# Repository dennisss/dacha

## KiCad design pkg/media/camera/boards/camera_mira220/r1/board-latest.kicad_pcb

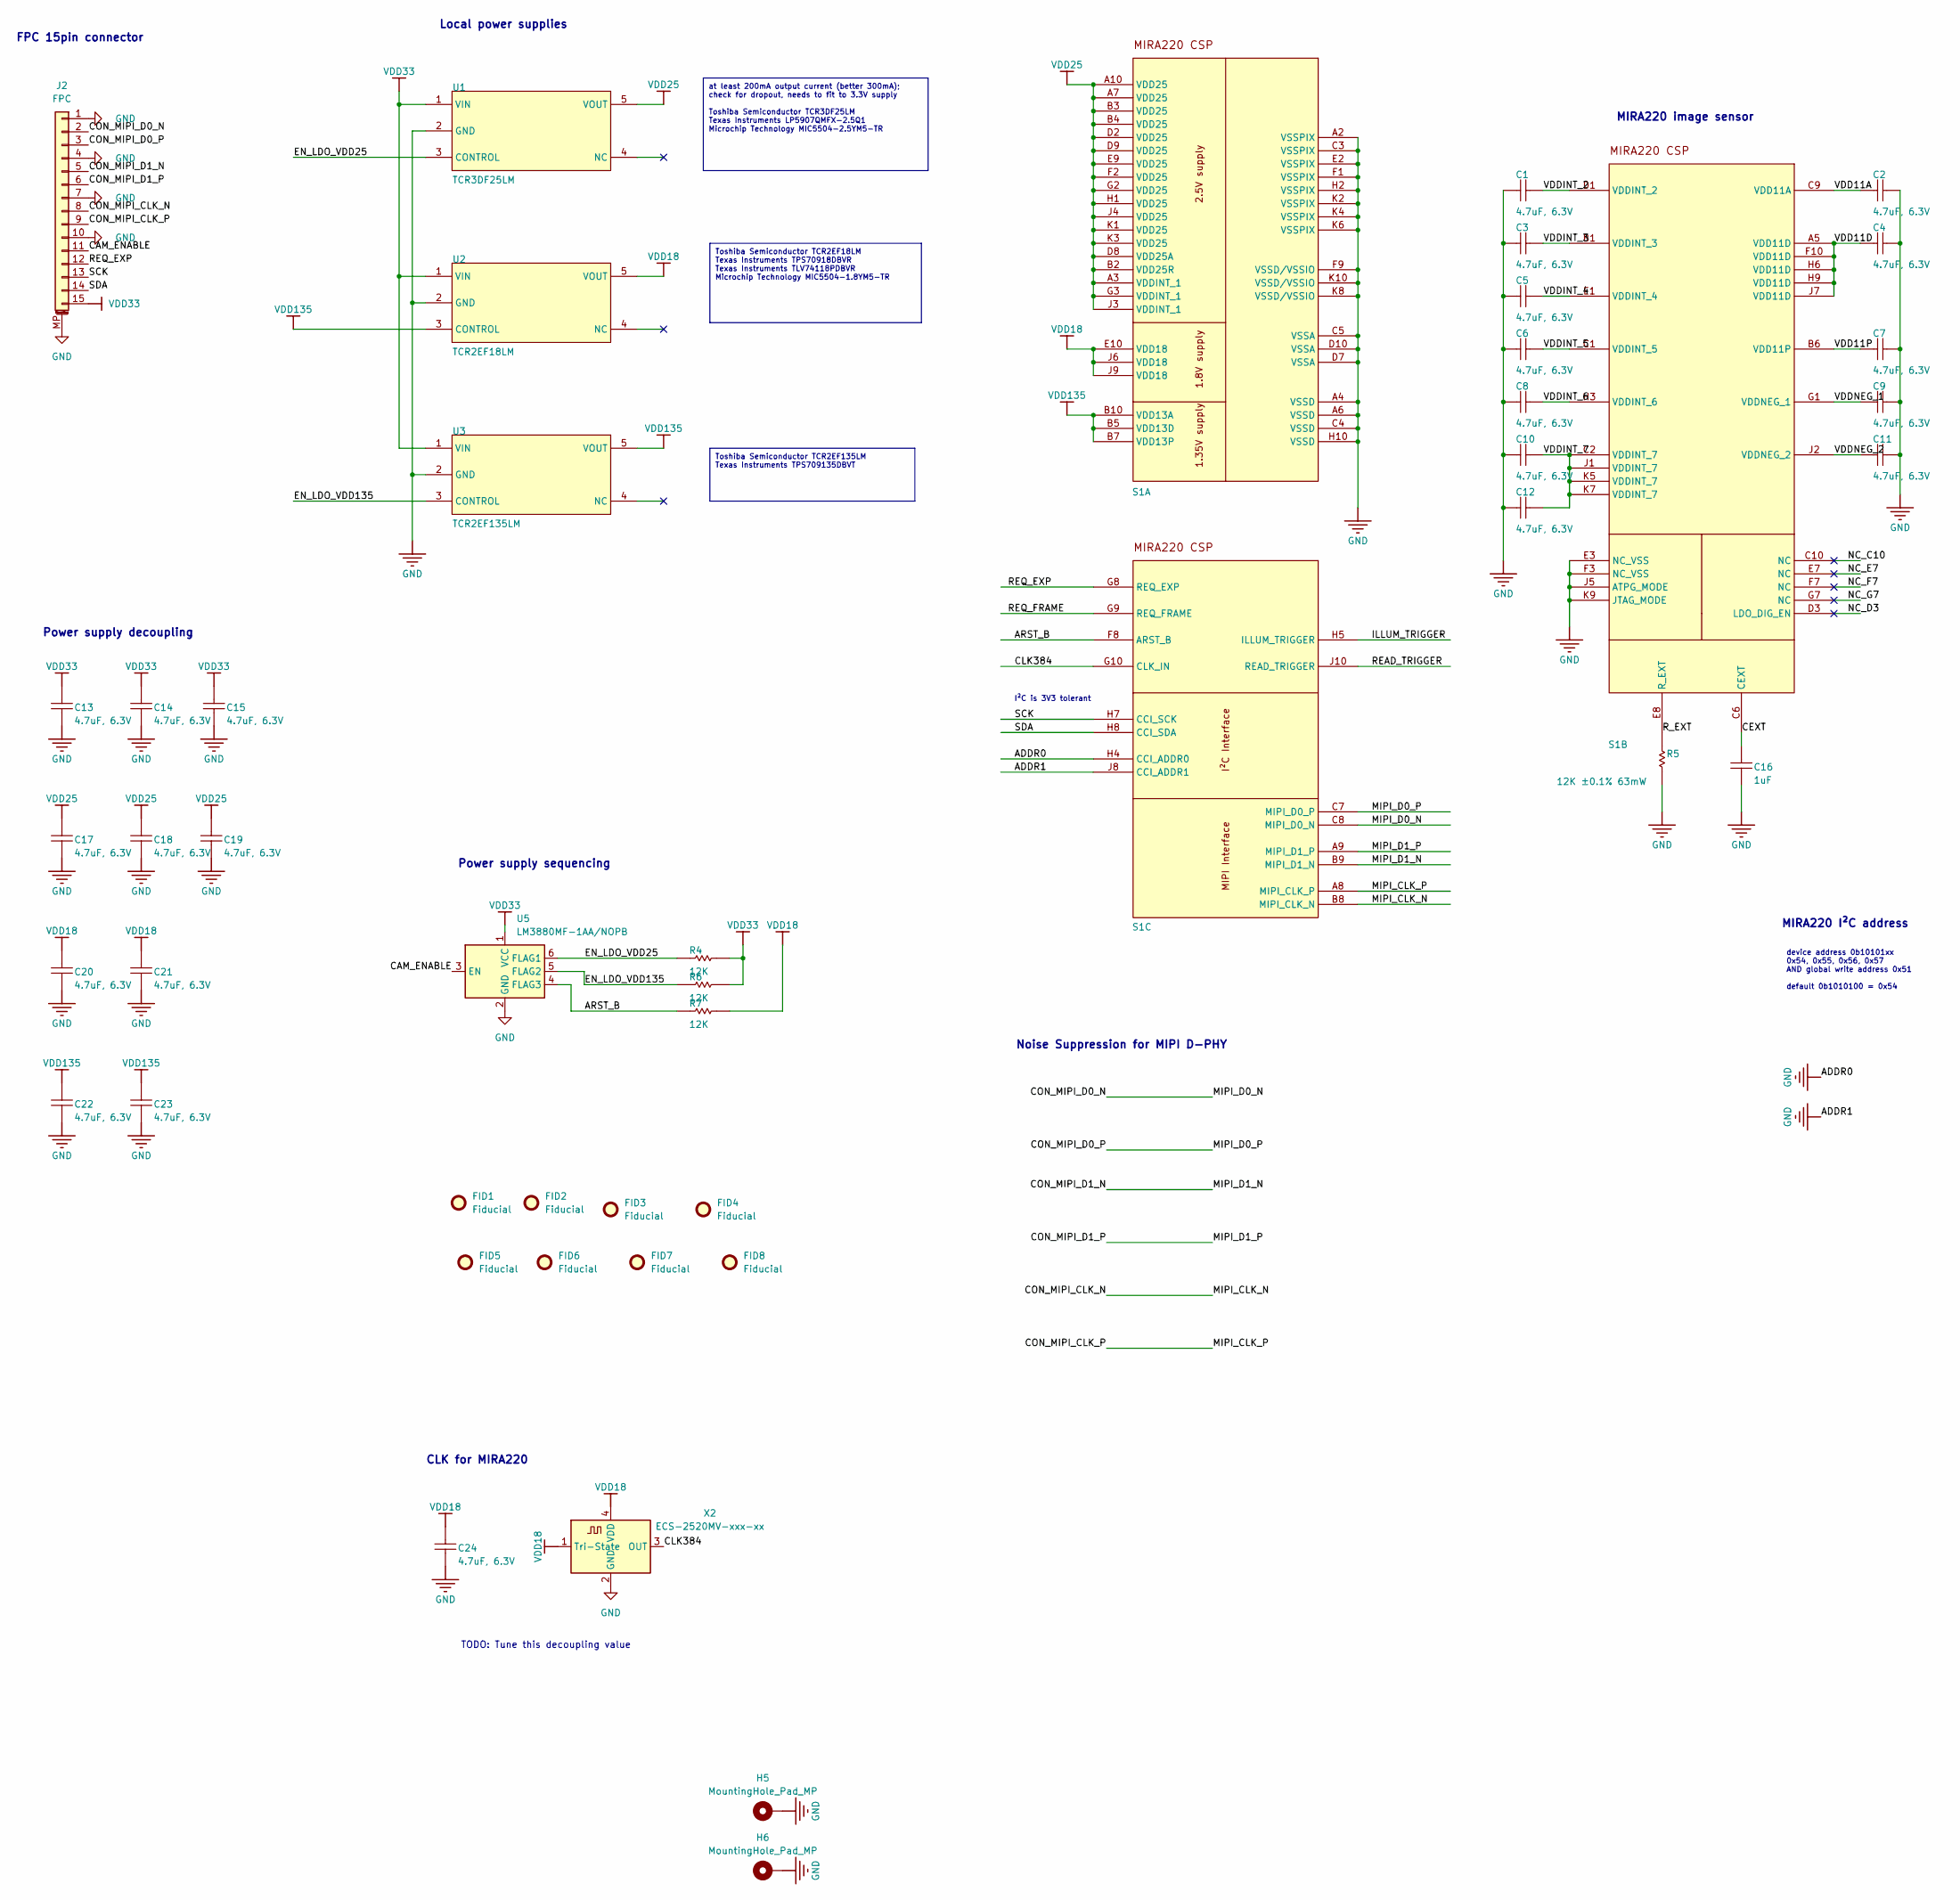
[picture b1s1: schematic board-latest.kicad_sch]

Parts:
C1, C2, C3, C4, C5, C6, C7, C8, C9, C10, C11, C13, C14, C15, C17, C18, C19, C20, C21, C22, C23, C24: 4.7uF, 6.3V; C_0402_1005Metric; RATED VOLTAGE 6.3; TOLERANCE ±10%; PART NUMBER GRM155R60J475ME47D
C12: 4.7uF, 6.3V; C_0402_1005Metric; RATED VOLTAGE 16 V; TOLERANCE ±10%; PART NUMBER GRM155R60J475ME47D
C16: 1uF; C_0402_1005Metric; PART NUMBER GRM155R70J105KA12J
FID1, FID2, FID3, FID4, FID5, FID6, FID7, FID8: Fiducial; Fiducial_1mm_Mask2mm
H5, H6: MountingHole_Pad_MP; MP_Lens
J2: FPC; TE_1-84952-5_1x15-1MP_P1.0mm_Horizontal
R4, R6, R7: 12K; R_0402_1005Metric; TOLERANCE ±0.1%; VOLTAGERATING 50V; PART NUMBER ERA2AEB123X
R5: 12K ±0.1% 63mW; R_0402_1005Metric; TOLERANCE ±0.1%; VOLTAGERATING 50V; PART NUMBER ERA2AEB123X
S1: MIRA CSP; MIRA220CSP; PART NUMBER Mira220-2QM1WA
U1: TCR3DF25LM; SC-74A-5_1.55x2.9mm_P0.95mm
U2: TCR2EF18LM; SC-74A-5_1.55x2.9mm_P0.95mm
U3: TCR2EF135LM; SC-74A-5_1.55x2.9mm_P0.95mm
U5: LM3880MF-1AA/NOPB; SOT-23-6
X2: ECS-2520MV-xxx-xx; Oscillator_SMD_ECS_2520MV-xxx-xx-4Pin_2.5x2.0mm

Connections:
/ARST_B: R7.2, S1.F8 (ARST_B), U5.4 (FLAG3)
/CAM_ENABLE: J2.11, U5.3 (EN)
/CEXT: C16.2, S1.C6 (CEXT)
/CLK384: S1.G10 (CLK_IN), X2.3 (OUT)
/CON_MIPI_CLK_N: J2.8, S1.B8 (MIPI_CLK_N)
/CON_MIPI_CLK_P: J2.9, S1.A8 (MIPI_CLK_P)
/CON_MIPI_D0_N: J2.2, S1.C8 (MIPI_D0_N)
/CON_MIPI_D0_P: J2.3, S1.C7 (MIPI_D0_P)
/CON_MIPI_D1_N: J2.5, S1.B9 (MIPI_D1_N)
/CON_MIPI_D1_P: J2.6, S1.A9 (MIPI_D1_P)
/EN_LDO_VDD25: R4.2, U1.3 (CONTROL), U5.6 (FLAG1)
/EN_LDO_VDD135: R6.2, U3.3 (CONTROL), U5.5 (FLAG2)
/ILLUM_TRIGGER: S1.H5 (ILLUM_TRIGGER)
/NC_C10: S1.C10 (NC)
/NC_D3: S1.D3 (LDO_DIG_EN)
/NC_E7: S1.E7 (NC)
/NC_F7: S1.F7 (NC)
/NC_G7: S1.G7 (NC)
/READ_TRIGGER: S1.J10 (READ_TRIGGER)
/REQ_EXP: J2.12, S1.G8 (REQ_EXP)
/REQ_FRAME: S1.G9 (REQ_FRAME)
/R_EXT: R5.2, S1.E8 (R_EXT)
/SCK: J2.13, S1.H7 (CCI_SCK)
/SDA: J2.14, S1.H8 (CCI_SDA)
/VDD11A: C2.1, S1.C9 (VDD11A)
/VDD11D: C4.1, S1.A5 (VDD11D), S1.F10 (VDD11D), S1.H6 (VDD11D), S1.H9 (VDD11D), S1.J7 (VDD11D)
/VDD11P: C7.1, S1.B6 (VDD11P)
/VDDINT_2: C1.2, S1.D1 (VDDINT_2)
/VDDINT_3: C3.2, S1.B1 (VDDINT_3)
/VDDINT_4: C5.2, S1.E1 (VDDINT_4)
/VDDINT_5: C6.2, S1.C1 (VDDINT_5)
/VDDINT_6: C8.2, S1.H3 (VDDINT_6)
/VDDINT_7: C10.2, C12.2, S1.C2 (VDDINT_7), S1.J1 (VDDINT_7), S1.K5 (VDDINT_7), S1.K7 (VDDINT_7)
/VDDNEG_1: C9.1, S1.G1 (VDDNEG_1)
/VDDNEG_2: C11.1, S1.J2 (VDDNEG_2)
GND: C1.1, C2.2, C3.1, C4.2, C5.1, C6.1, C7.2, C8.1, C9.2, C10.1, C11.2, C12.1, C13.1, C14.1, C15.1, C16.1, C17.1, C18.1, C19.1, C20.1, C21.1, C22.1, C23.1, C24.1, H5.MP, H6.MP, J2.1, J2.4, J2.7, J2.10, J2.MP (MountPin), R5.1, S1.A2 (VSSPIX), S1.A4 (VSSD), S1.A6 (VSSD), S1.C3 (VSSPIX), S1.C4 (VSSD), S1.C5 (VSSA), S1.D7 (VSSA), S1.D10 (VSSA), S1.E2 (VSSPIX), S1.E3 (NC_VSS), S1.F1 (VSSPIX), S1.F3 (NC_VSS), S1.F9 (VSSD/VSSIO), S1.H2 (VSSPIX), S1.H4 (CCI_ADDR0), S1.H10 (VSSD), S1.J5 (ATPG_MODE), S1.J8 (CCI_ADDR1), S1.K2 (VSSPIX), S1.K4 (VSSPIX), S1.K6 (VSSPIX), S1.K8 (VSSD/VSSIO), S1.K9 (JTAG_MODE), S1.K10 (VSSD/VSSIO), U1.2 (GND), U2.2 (GND), U3.2 (GND), U5.2 (GND), X2.2 (GND)
VDD18: C20.2, C21.2, C24.2, R7.1, S1.E10 (VDD18), S1.J6 (VDD18), S1.J9 (VDD18), U2.5 (VOUT), X2.1 (Tri-State), X2.4 (VDD)
VDD25: C17.2, C18.2, C19.2, S1.A3 (VDDINT_1), S1.A7 (VDD25), S1.A10 (VDD25), S1.B2 (VDD25R), S1.B3 (VDD25), S1.B4 (VDD25), S1.D2 (VDD25), S1.D8 (VDD25A), S1.D9 (VDD25), S1.E9 (VDD25), S1.F2 (VDD25), S1.G2 (VDD25), S1.G3 (VDDINT_1), S1.H1 (VDD25), S1.J3 (VDDINT_1), S1.J4 (VDD25), S1.K1 (VDD25), S1.K3 (VDD25), U1.5 (VOUT)
VDD33: C13.2, C14.2, C15.2, J2.15, R4.1, R6.1, U1.1 (VIN), U2.1 (VIN), U3.1 (VIN), U5.1 (VCC)
VDD135: C22.2, C23.2, S1.B5 (VDD13D), S1.B7 (VDD13P), S1.B10 (VDD13A), U2.3 (CONTROL), U3.5 (VOUT)

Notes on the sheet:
MIRA220 image sensor
I²C is 3V3 tolerant
Noise Suppression for MIPI D-PHY
Power supply decoupling
MIRA220 I²C address
Power supply sequencing
TODO: Tune this decoupling value
CLK for MIRA220
Local power supplies
FPC 15pin connector
at least 200mA output current (better 300mA); check for dropout, needs to fit to 3.3V supply Toshiba Semiconductor TCR3DF25LM Texas Instruments LP5907QMFX-2.5Q1 Microchip Technology MIC5504-2.5YM5-TR
device address 0b10101xx 0x54, 0x55, 0x56, 0x57 AND global write address 0x51 default 0b1010100 = 0x54
Toshiba Semiconductor TCR2EF18LM Texas Instruments TPS70918DBVR Texas Instruments TLV74118PDBVR Microchip Technology MIC5504-1.8YM5-TR
Toshiba Semiconductor TCR2EF135LM Texas Instruments TPS709135DBVT

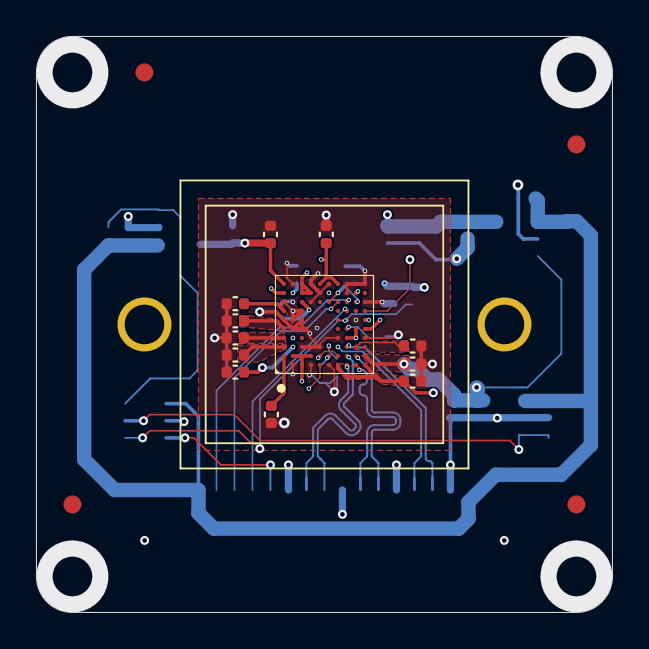
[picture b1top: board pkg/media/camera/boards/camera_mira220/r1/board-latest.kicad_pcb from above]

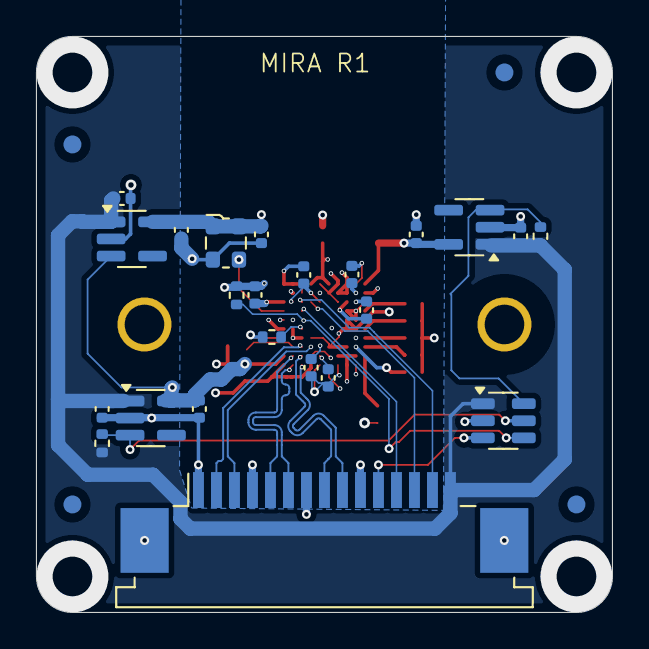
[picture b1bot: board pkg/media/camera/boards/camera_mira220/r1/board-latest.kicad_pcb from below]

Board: 6 copper layers, 32.0 x 32.0 mm, 45 parts (27 on the bottom side), 32 nets.

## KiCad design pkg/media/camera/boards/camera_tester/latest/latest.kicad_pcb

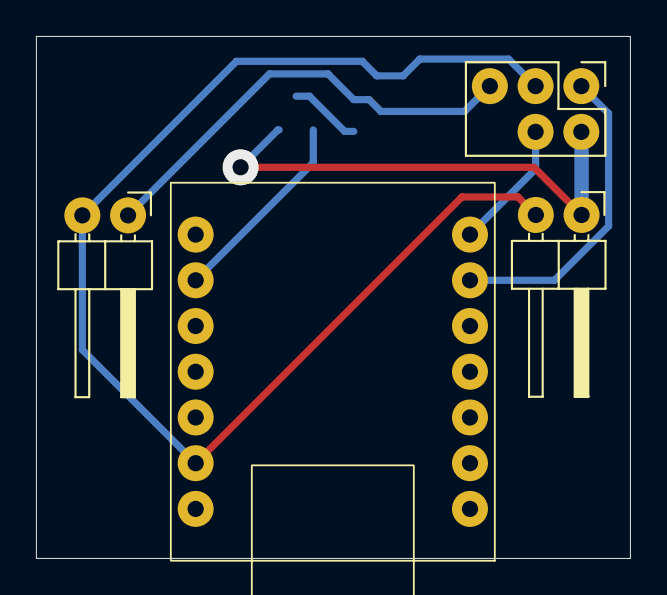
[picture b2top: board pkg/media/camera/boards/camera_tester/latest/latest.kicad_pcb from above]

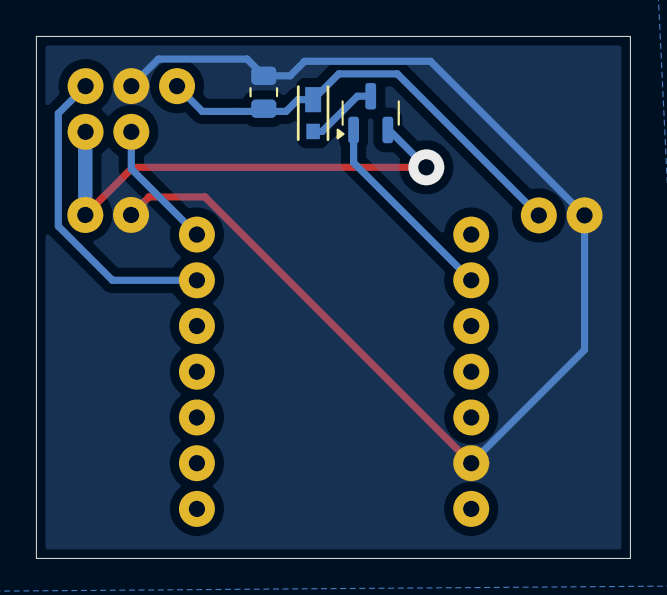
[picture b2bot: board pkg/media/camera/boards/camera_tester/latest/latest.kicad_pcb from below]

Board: 2 copper layers, 33.0 x 29.0 mm, 7 parts (3 on the bottom side), 7 nets.

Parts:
CR1: MSS1P3L-M3/89A; DIODE_MSP3V3
J1: FPC; PinHeader_2x03_P2.54mm_Vertical
J2: POWER; PinHeader_1x02_P2.54mm_Horizontal
J3: UDPI; PinHeader_1x02_P2.54mm_Horizontal
Q2: AO3401A; SOT-23
R1: 100K; R_0805_2012Metric
U1: XIAO_NRF52840

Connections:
+3V3: J1.2, J2.1, Q2.2 (S)
ENABLE: CR1.1, J1.5, J3.1, R1.1
ENABLE_DRIVE_HIGH: Q2.1 (G), U1.9 (P1.13)
GND: J1.3, J2.2, J3.2, R1.2, U1.13 (GND)
unnamed: CR1.2, Q2.3 (D)
SCL: J1.4, U1.7 (P1.11)
SDA: J1.1, U1.6 (P0.05(A5))

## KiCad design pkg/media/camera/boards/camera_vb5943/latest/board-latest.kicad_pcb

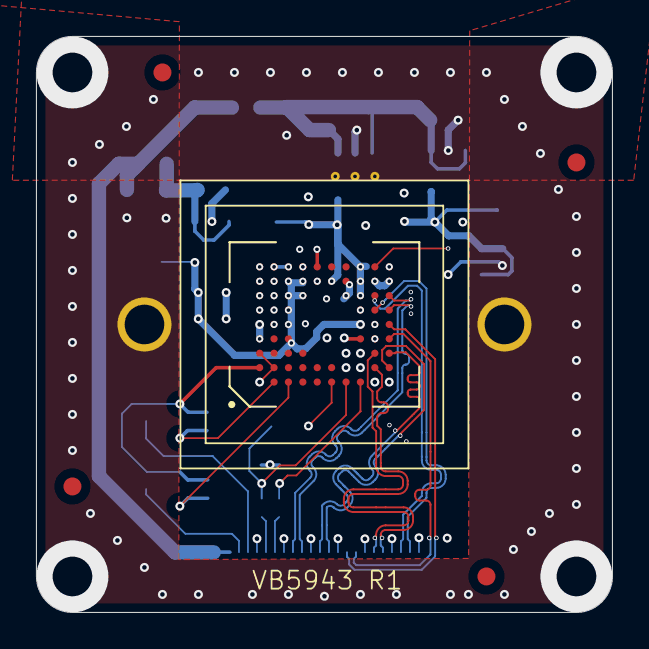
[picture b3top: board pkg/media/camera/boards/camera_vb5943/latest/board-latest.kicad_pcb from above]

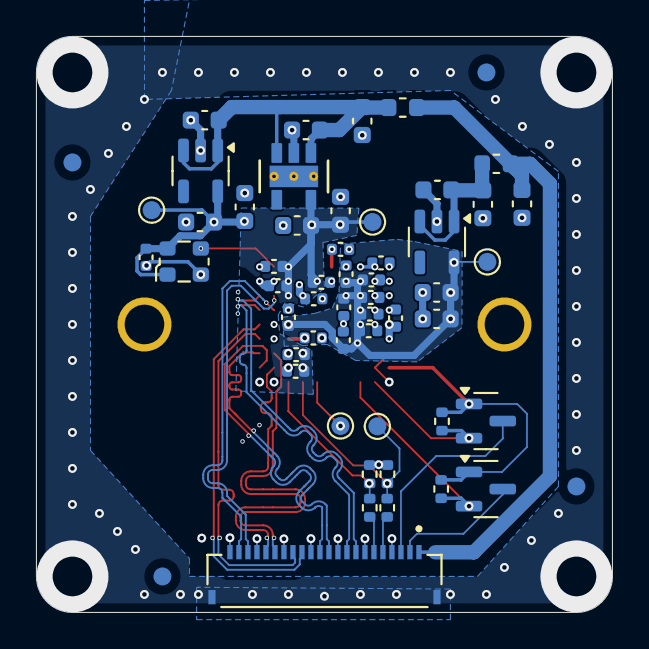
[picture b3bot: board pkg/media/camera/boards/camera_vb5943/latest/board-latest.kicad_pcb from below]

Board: 6 copper layers, 32.0 x 32.0 mm, 62 parts (55 on the bottom side), 31 nets.

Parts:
C1, C3, C4, C5, C6, C7, C8, C9, C20, C21, C29: 0.1uF; C_0402_1005Metric
C30, C31, C32, C33, C34, C35: 1uF; C_0603_1608Metric
C37, C38, C39, C40, C41, C50: 10uF; C_0603_1608Metric
C42: 4.7uF; C_0402_1005Metric
C43, C46, C47, C48: 470nF; C_0402_1005Metric
C44, C49: 1uF; C_0402_1005Metric
C45: 10uF; C_0402_1005Metric
FID1, FID2, FID3, FID4, FID5, FID6, FID7, FID8: Fiducial; Fiducial_1mm_Mask2mm
H5, H6: MountingHole_Pad_MP; MP_Lens
J1: FH34SRJ-22S-0.5SH_50_; HRS_FH34SRJ-22S-0.5SH_50_
L1, L2: 600 ohm; L_0603_1608Metric
Q1, Q2: BSS138; SOT-23
R2, R3, R4, R6, R14, R15: 1.5K; R_0402_1005Metric
TP1: FLASH; TestPoint_Pad_D1.0mm
TP2: TRIGGER; TestPoint_Pad_D1.0mm
TP3: 2V8; TestPoint_Pad_D1.0mm
TP4: 1V8; TestPoint_Pad_D1.0mm
TP5: 1V2; TestPoint_Pad_D1.0mm
U3: NCP163ASN280T1G; SOT-23-5
U4: TLV74318PDBVR; SOT-23-5
U5: TLV75512PDYDR; DYD0005A-MFG
U6: VB5943; VB5943_BGA
X1: ECS-2520MV-240-DN-TR; Oscillator_SMD_ECS_2520MV-xxx-xx-4Pin_2.5x2.0mm

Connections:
+1V2: C20.1, C21.1, C34.1, C38.1, C46.2, C47.2, C48.2, TP5.1, U5.5 (OUT), U6.F8 (VCORE), U6.G2 (VCORE), U6.G3 (VCORE), U6.H7 (VCORE), U6.H8 (VCORE), U6.H9 (VCORE)
+1V8: C29.1, C33.1, C49.1, C50.1, Q1.1 (G), Q2.1 (G), R4.2, R6.2, TP4.1, U4.5 (OUT), U6.A2 (CLK_RANGE0), U6.G7 (VDDIO), U6.G8 (VDDIO), X1.1 (Tri-State), X1.4 (VDD)
+2V8: C1.1, C3.1, C4.1, C5.1, C6.1, C7.1, C8.1, C9.1, C31.1, C37.1, TP3.1, U3.5 (OUT), U6.C4 (VANA), U6.C5 (VANA), U6.C6 (VANA), U6.C7 (VANA), U6.C8 (VANA), U6.D7 (VANA), U6.D8 (VANA), U6.H5 (VANA)
+3V3: C41.1, J1.1, L1.1, L2.1
ANALOG_3V3: C30.1, C39.1, L1.2, U3.1 (IN), U3.3 (EN)
DIGITAL_3V3: C32.1, C35.1, C40.1, L2.2, U4.1 (IN), U4.3 (EN), U5.1 (IN), U5.3 (EN)
ENABLE_1V8: R14.1, R15.2, U6.H1 (~RESET)
ENABLE_3V3: J1.6, R14.2
EXTCLK: U6.J9 (EXTCLK), X1.3 (OUT)
GND: C1.2, C3.2, C4.2, C5.2, C6.2, C7.2, C8.2, C9.2, C20.2, C21.2, C29.2, C30.2, C31.2, C32.2, C33.2, C34.2, C35.2, C37.2, C38.2, C39.2, C40.2, C41.2, C42.1, C43.1, C44.2, C45.2, C46.1, C47.1, C48.1, C49.2, C50.2, H5.MP, H6.MP, J1.4, J1.7, J1.10, J1.13, J1.16, J1.19, J1.22, J1.S1 (SHIELD), J1.S2 (SHIELD), R3.1, R15.1, U3.2 (GND), U4.2 (GND), U5.2 (GND), U6.A1 (AGND), U6.A3 (CLK_RANGE1), U6.A6 (AGND), U6.A7 (AGND), U6.A8 (AGND), U6.A9 (AGND), U6.B2 (PORTEST), U6.B5 (AGND), U6.B6 (AGND), U6.B7 (AGND), U6.B8 (AGND), U6.D9 (AGND), U6.E8 (DGND), U6.H2 (DGND), U6.H3 (DGND), U6.H6 (AGND), U6.J1 (DGND), U6.J4 (DGND), U6.J5 (DGND), U6.J8 (DGND), U6.K1 (DGND), U6.K8 (DGND), U6.K9 (DGND), X1.2 (GND)
MIPI_CLK_N: J1.15, U6.K4 (CLKN)
MIPI_CLK_P: J1.14, U6.K5 (CLKP)
MIPI_D0_N: J1.21, U6.J6 (DATA1N)
MIPI_D0_P: J1.20, U6.J7 (DATA1P)
MIPI_D1_N: J1.18, U6.J2 (DATA2N)
MIPI_D1_P: J1.17, U6.J3 (DATA2P)
MIPI_D2_N: J1.12, U6.K2 (DATA3N)
MIPI_D2_P: J1.11, U6.K3 (DATA3P)
MIPI_D3_N: J1.9, U6.K6 (DATA4N)
MIPI_D3_P: J1.8, U6.K7 (DATA4P)
unnamed: C45.1, U6.A4 (CP_NEG_OUT), U6.A5 (CP_NEG_IN)
unnamed: C44.1, U6.B9 (CP_POS_OUT), U6.C9 (CP_POS_IN)
unnamed: TP1.1, U6.F1 (GPIO1)
unnamed: C43.2, U6.H4 (LDO2V4)
unnamed: C42.2, U6.E9 (VRT)
SCL_1V8: Q1.2 (S), R4.1, U6.B1 (SCL)
SCL_3V3: J1.3, Q1.3 (D)
SDA_1V8: Q2.2 (S), R6.1, U6.C1 (SDA)
SDA_3V3: J1.2, Q2.3 (D)
TRIGGER_1V8: R2.1, R3.2, TP2.1, U6.G1 (GPIO0)
TRIGGER_3V3: J1.5, R2.2

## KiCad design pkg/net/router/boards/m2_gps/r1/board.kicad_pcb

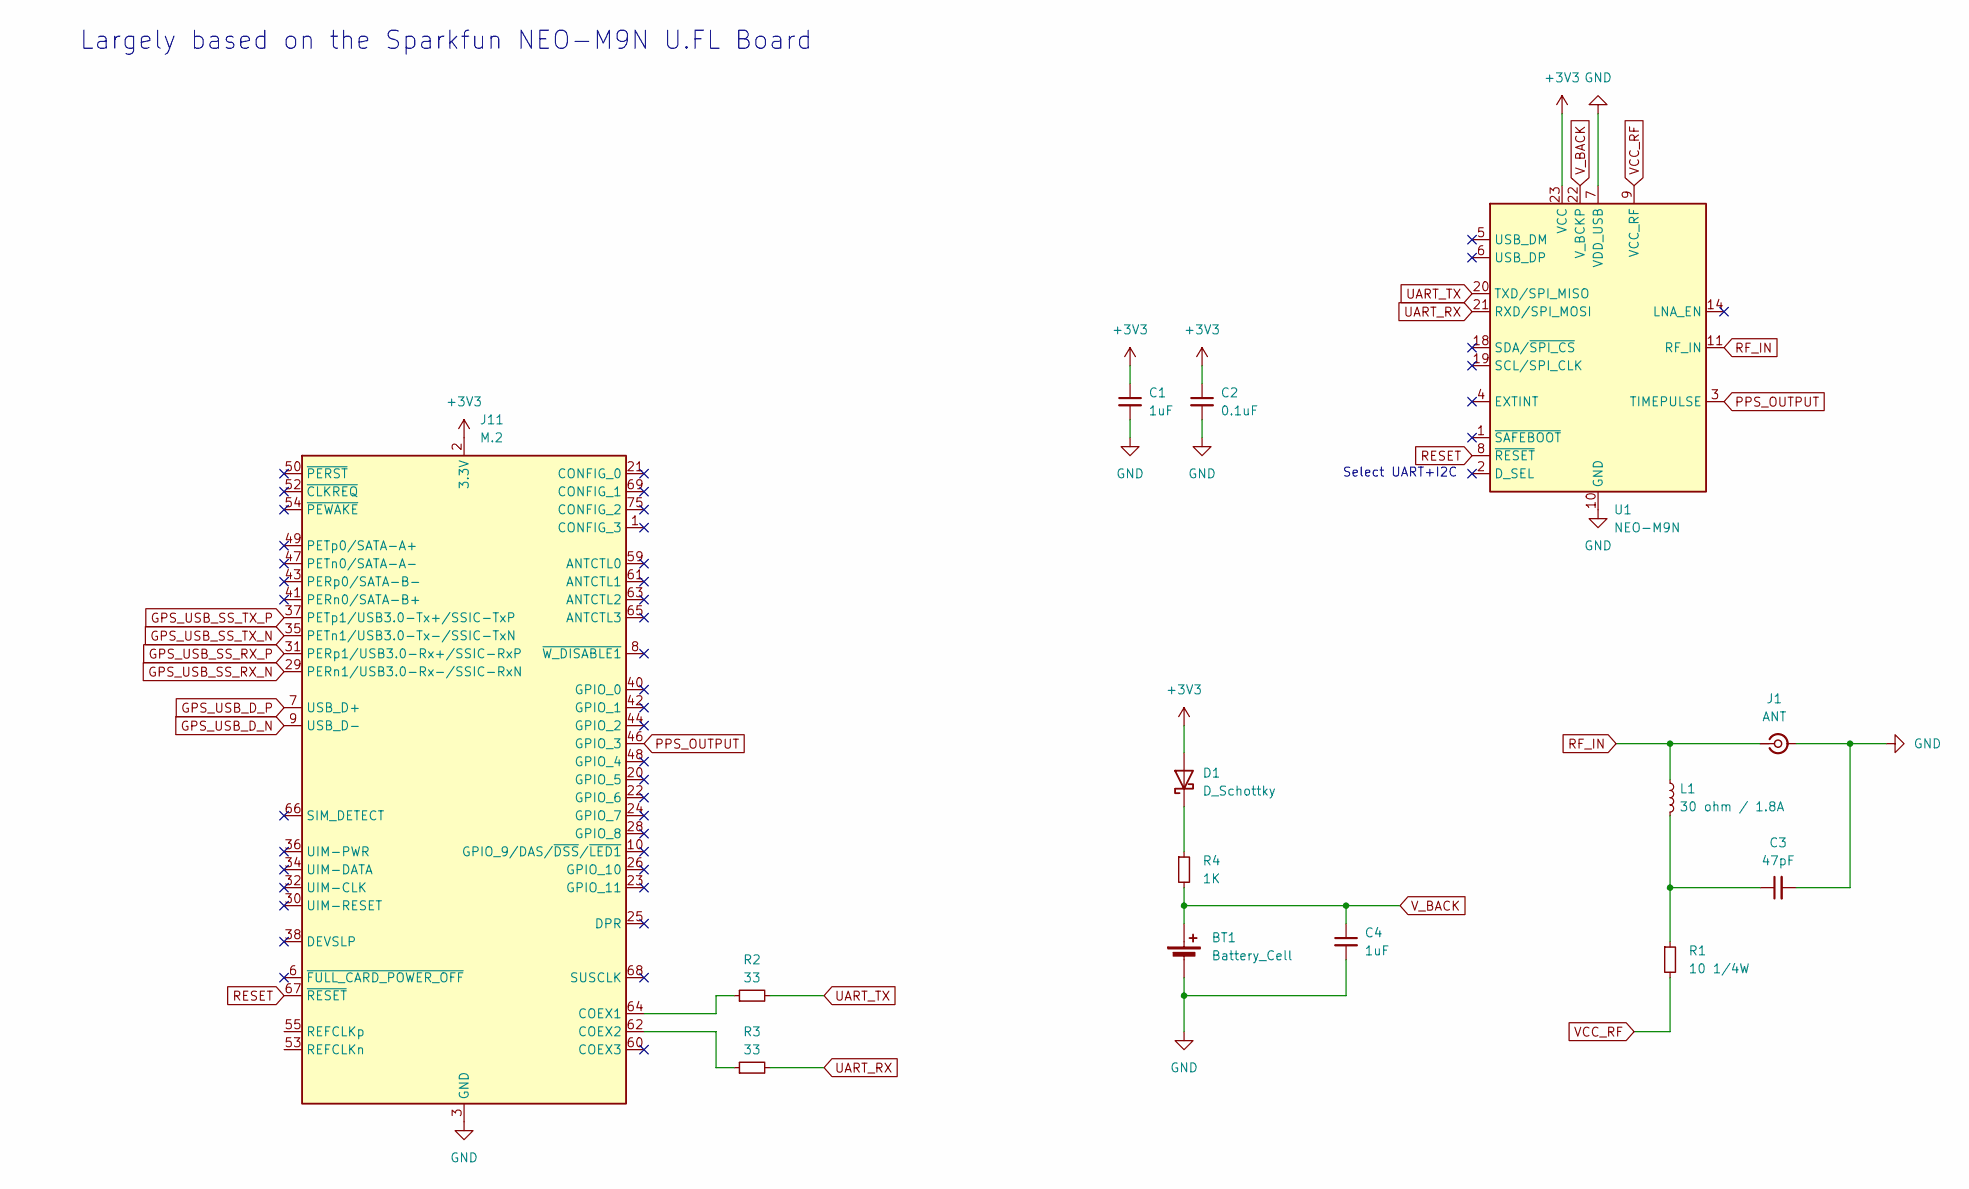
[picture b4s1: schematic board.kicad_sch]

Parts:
BT1: Battery_Cell; BAT_MS621FE-FL11E
C1, C4: 1uF; C_0603_1608Metric
C2: 0.1uF; C_0603_1608Metric
C3: 47pF; C_0603_1608Metric
D1: D_Schottky; D_SOD-523
J1: ANT; U.FL_Hirose_U.FL-R-SMT-1_Vertical
J11: M.2; M.2-B-KEY
L1: 30 ohm / 1.8A; L_0603_1608Metric
R1: 10 1/4W; R_0603_1608Metric
R2, R3: 33; R_0603_1608Metric
R4: 1K; R_0603_1608Metric
U1: NEO-M9N; ublox_NEO

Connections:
+3V3: C1.1, C2.1, D1.2 (A), J11.2 (3.3V), J11.4 (3.3V), J11.70 (3.3V), J11.72 (3.3V), J11.74 (3.3V), U1.23 (VCC)
GND: BT1.2 (-), C1.2, C2.2, C3.2, C4.2, J1.2 (Ext), J11.3 (GND), J11.5 (GND), J11.11 (GND), J11.27 (GND), J11.33 (GND), J11.39 (GND), J11.45 (GND), J11.51 (GND), J11.57 (GND), J11.71 (GND), J11.73 (GND), U1.7 (VDD_USB), U1.10 (GND), U1.12 (GND), U1.13 (GND), U1.24 (GND)
GPS_USB_D_N: J11.9 (USB_D-)
GPS_USB_D_P: J11.7 (USB_D+)
GPS_USB_SS_RX_N: J11.29 (PERn1/USB3.0-Rx-/SSIC-RxN)
GPS_USB_SS_RX_P: J11.31 (PERp1/USB3.0-Rx+/SSIC-RxP)
GPS_USB_SS_TX_N: J11.35 (PETn1/USB3.0-Tx-/SSIC-TxN)
GPS_USB_SS_TX_P: J11.37 (PETp1/USB3.0-Tx+/SSIC-TxP)
unnamed: C3.1, L1.2, R1.1
unnamed: D1.1 (K), R4.1
unnamed: J11.64 (COEX1), R2.1
unnamed: J11.62 (COEX2), R3.1
PPS_OUTPUT: J11.46 (GPIO_3), U1.3 (TIMEPULSE)
RESET: J11.67 (~RESET), U1.8 (~RESET)
RF_IN: J1.1 (In), L1.1, U1.11 (RF_IN)
UART_RX: R3.2, U1.21 (RXD/SPI_MOSI)
UART_TX: R2.2, U1.20 (TXD/SPI_MISO)
VCC_RF: R1.2, U1.9 (VCC_RF)
V_BACK: BT1.1 (+), C4.1, R4.2, U1.22 (V_BCKP)

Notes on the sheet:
Largely based on the Sparkfun NEO-M9N U.FL Board
Select UART+I2C

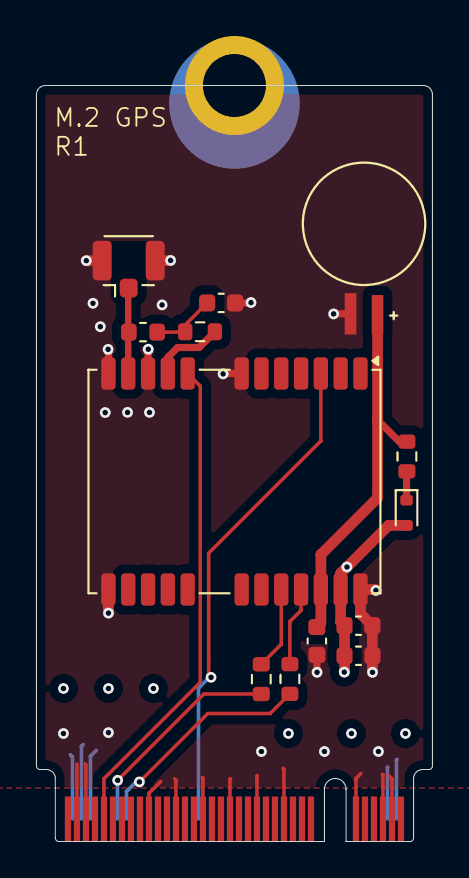
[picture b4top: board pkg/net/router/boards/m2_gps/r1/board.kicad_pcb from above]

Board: 4 copper layers, 22.0 x 42.0 mm, 14 parts (0 on the bottom side), 13 nets.

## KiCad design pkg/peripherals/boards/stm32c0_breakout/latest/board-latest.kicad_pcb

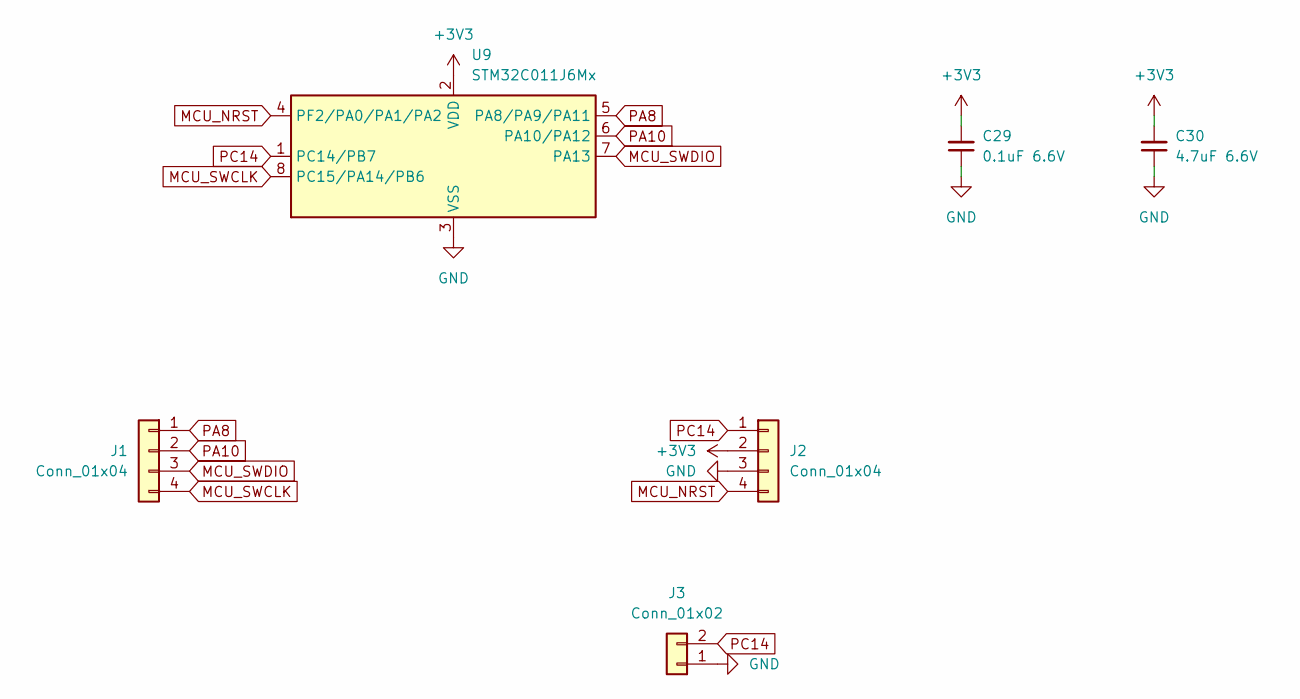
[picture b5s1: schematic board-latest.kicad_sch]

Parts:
C29: 0.1uF 6.6V; C_0603_1608Metric
C30: 4.7uF 6.6V; C_0603_1608Metric
J1, J2: Conn_01x04; PinHeader_1x04_P2.54mm_Horizontal
J3: Conn_01x02; PinHeader_1x02_P2.54mm_Horizontal
U9: STM32C011J6Mx; SOIC-8_3.9x4.9mm_P1.27mm

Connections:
+3V3: C29.2, C30.2, J2.2, U9.2 (VDD)
GND: C29.1, C30.1, J2.3, J3.1, U9.3 (VSS)
MCU_NRST: J2.4, U9.4 (PF2/PA0/PA1/PA2)
MCU_SWCLK: J1.4, U9.8 (PC15/PA14/PB6)
MCU_SWDIO: J1.3, U9.7 (PA13)
PA8: J1.1, U9.5 (PA8/PA9/PA11)
PA10: J1.2, U9.6 (PA10/PA12)
PC14: J2.1, J3.2, U9.1 (PC14/PB7)

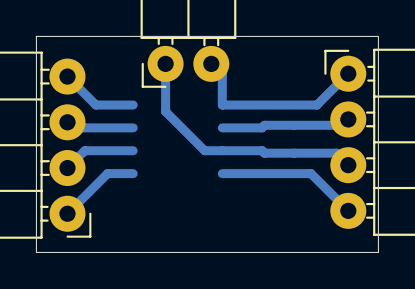
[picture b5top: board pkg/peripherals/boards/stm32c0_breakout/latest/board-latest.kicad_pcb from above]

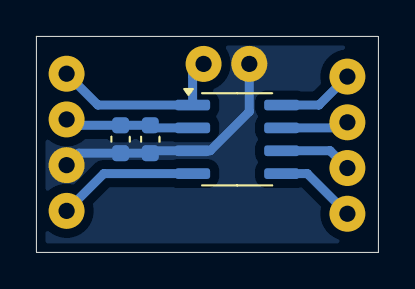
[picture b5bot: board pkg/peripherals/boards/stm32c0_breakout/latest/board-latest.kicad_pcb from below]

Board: 2 copper layers, 19.0 x 12.0 mm, 6 parts (3 on the bottom side), 8 nets.

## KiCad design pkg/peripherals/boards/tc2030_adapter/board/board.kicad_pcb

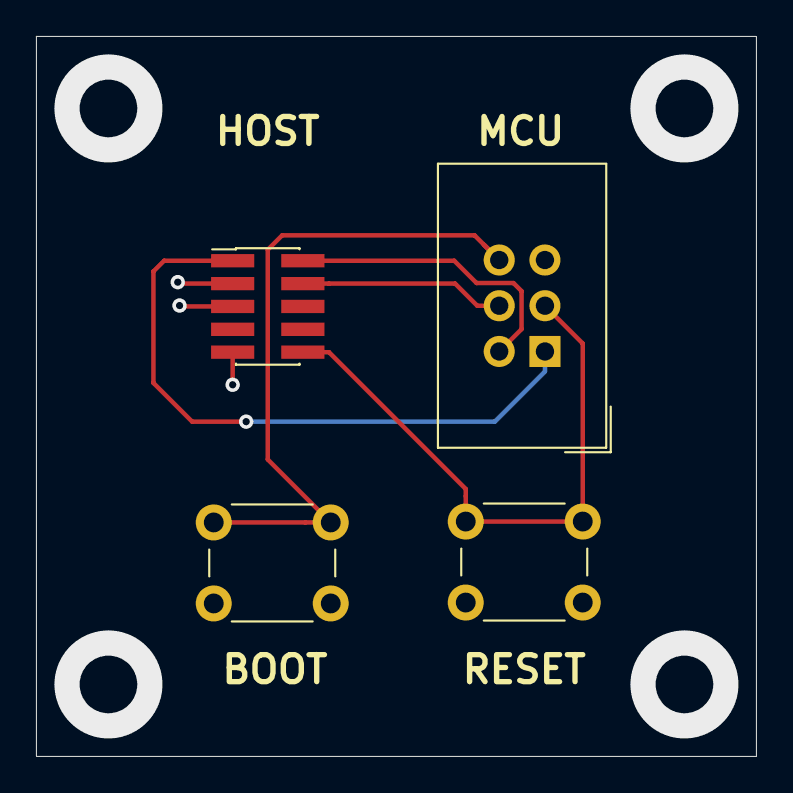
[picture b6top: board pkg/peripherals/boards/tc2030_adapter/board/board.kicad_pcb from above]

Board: 2 copper layers, 40.0 x 40.0 mm, 4 parts (0 on the bottom side), 6 nets.

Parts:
J1: Conn_02x03_Odd_Even; IDC-Header_2x03_P2.54mm_Vertical
J2: Conn_02x05_Odd_Even; PinHeader_2x05_P1.27mm_Vertical_SMD
SW1, SW2: SW_Push; SW_PUSH_6mm

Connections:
BOOTSEL: J1.6, SW2.1
GND: J1.5, J2.3, J2.5, J2.9, SW1.2, SW2.2
RESET: J1.3, J2.10, SW1.1
SWDCLK: J1.4, J2.4
SWDIO: J1.2, J2.2
VREF: J1.1, J2.1

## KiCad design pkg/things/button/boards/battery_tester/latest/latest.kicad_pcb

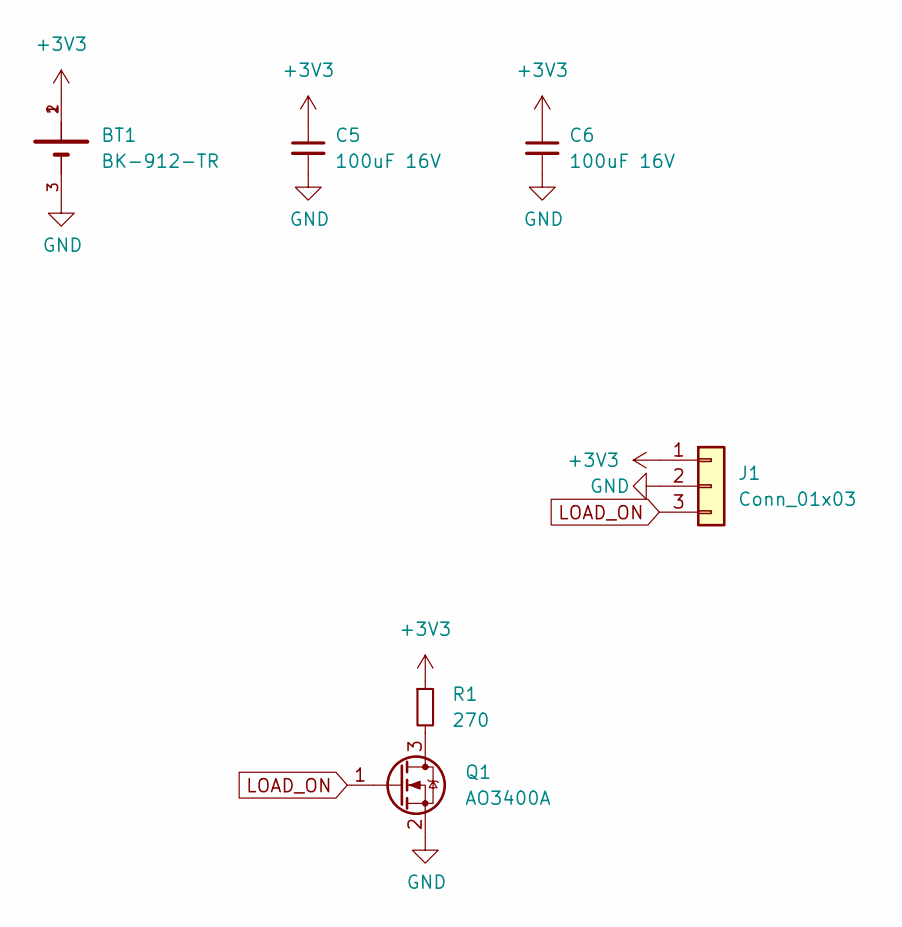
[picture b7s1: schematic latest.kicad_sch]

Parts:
BT1: BK-912-TR; MPD_BK-912-TR; PARTREV H
C5, C6: 100uF 16V; C_1210_3225Metric
J1: Conn_01x03; PinHeader_1x03_P2.54mm_Horizontal
Q1: AO3400A; SOT-23
R1: 270; C_0805_2012Metric_Pad1.18x1.45mm_HandSolder

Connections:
+3V3: BT1.1, BT1.2, C5.1, C6.1, J1.1, R1.1
GND: BT1.3, C5.2, C6.2, J1.2, Q1.2 (S)
LOAD_ON: J1.3, Q1.1 (G)
unnamed: Q1.3 (D), R1.2

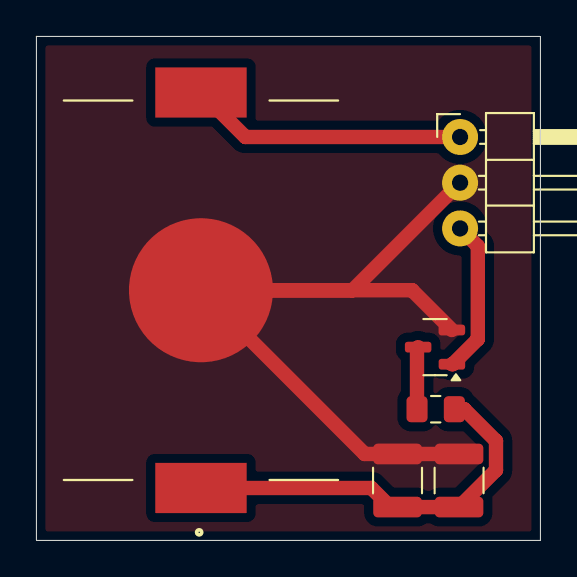
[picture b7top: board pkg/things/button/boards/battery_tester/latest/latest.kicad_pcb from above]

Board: 2 copper layers, 28.0 x 28.0 mm, 6 parts (0 on the bottom side), 4 nets.
